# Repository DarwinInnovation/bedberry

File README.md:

# bedberry

PCB for intelligent electric bed/chair control. A board to allow those with disabilities
a number of ways to control electric beds, chairs etc.

Based around the [Raspberry Pi Zero 2W](https://www.raspberrypi.com/products/raspberry-pi-zero-2-w/) it is designed to allow abilities such as:

- Voice service (e.g. Alexa) control of the bed.
- Control of all the bed's function from simple buttons or pressure pads.
- Link to BLE tilt sensors to allow bed position 'presets'.
- Control of other devices via bluetooth, IR or WiFi, including TVs, lights, SwitchBots etc.

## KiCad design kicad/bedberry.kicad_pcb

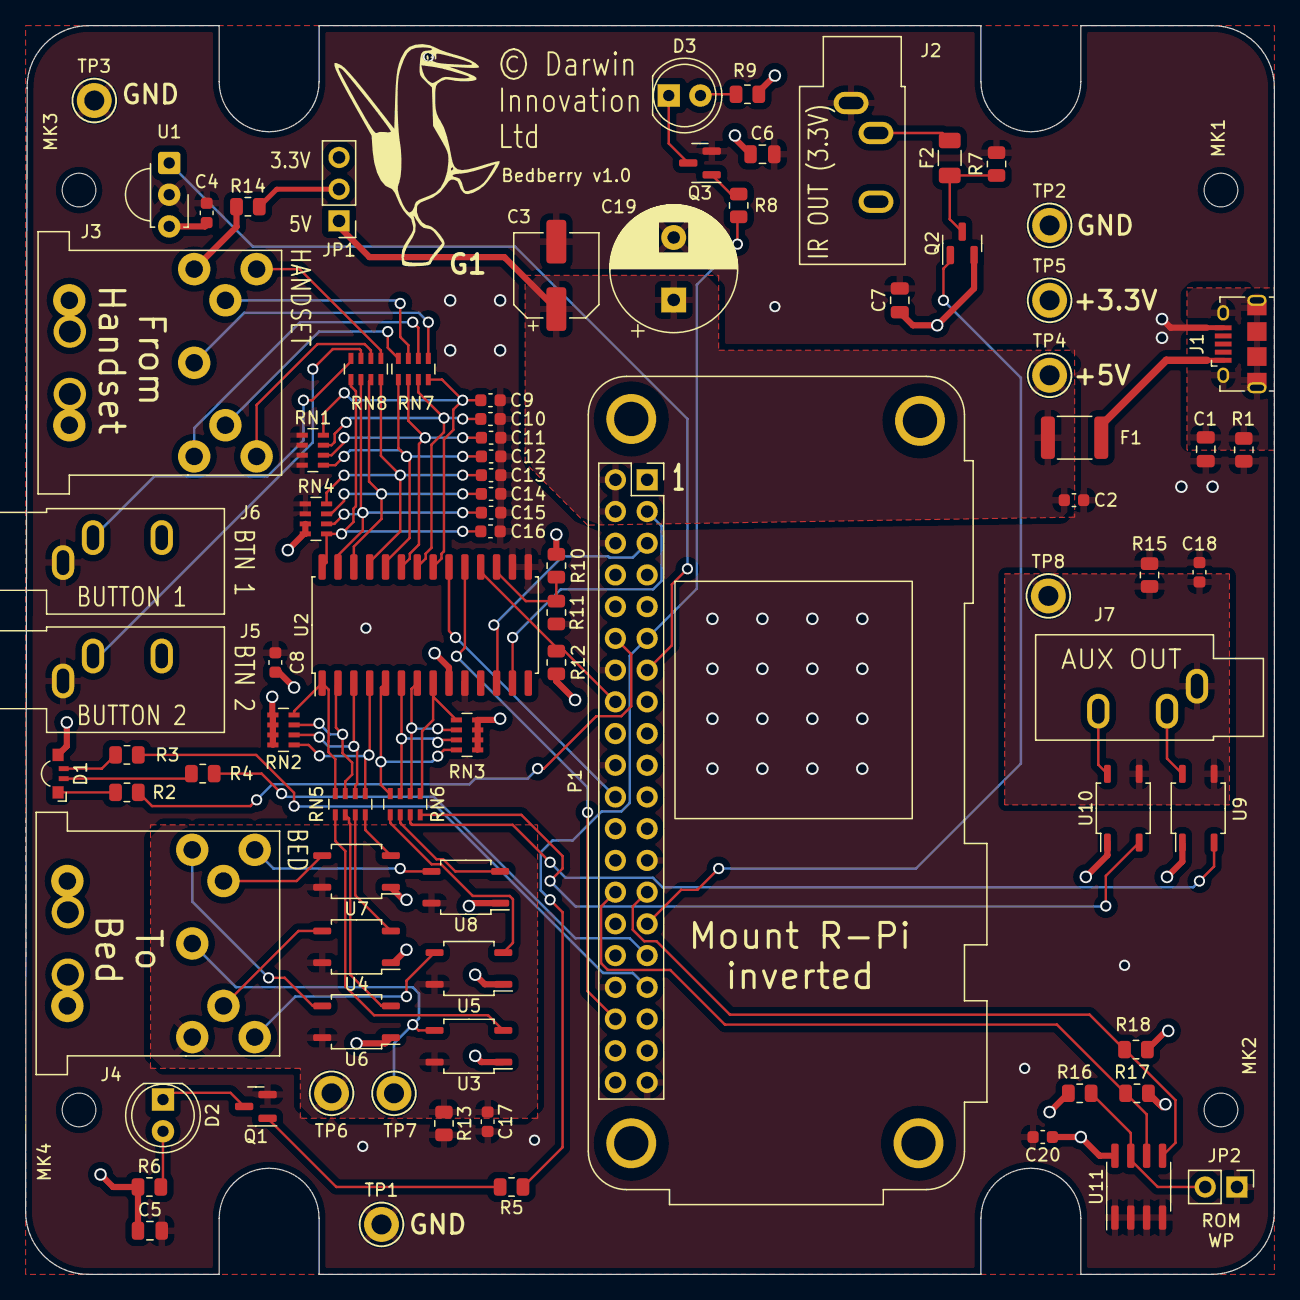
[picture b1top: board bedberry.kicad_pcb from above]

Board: 4 copper layers, 100.0 x 100.0 mm, 88 parts (0 on the bottom side), 75 nets.

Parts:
C1: 1nF 0805; C_0805_2012Metric
C2, C4, C8, C9, C10, C11, C12, C13, C14, C15, C16, C17, C18, C20: 100nF 0603; C_0603_1608Metric
C3: 100uF SMD; CP_Elec_6.3x7.7
C5, C6, C7: 1uF 0805; C_0805_2012Metric
C19: 100uF 10mm TH; CP_Radial_D10.0mm_P5.00mm
D1: KPFA-3010RGBC-11; LED_Kingbright_APFA3010_3x1.5mm_Horizontal
D2, D3: SFH4546; LED_D5.0mm_IRGrey
F1: MP005240; Fuse_1812_4532Metric
F2: 1206L150THWR; Fuse_1206_3216Metric
G1: LOGO; darwin_innovation_logo
J1: USB Micro-B; USB_Micro-B_Amphenol_10118194_Horizontal
J2, J5, J6, J7: SJ1-3533NG; Jack_3.5mm_CUI_SJ1-3533NG_Horizontal
J3, J4: DIN-7; pro-signal_DIN7_Socket
JP1: Jumper; PinHeader_1x03_P2.54mm_Vertical
JP2: Jumper_2_Open; PinHeader_1x02_P2.54mm_Vertical
MK1, MK2, MK3, MK4: M2.5; MountingHole_2.7mm_M2.5
P1: RPi Zero 2 W; Raspberry_Pi_Zero_2W_Socketed_THT_FaceDown_MountingHoles
Q1, Q3: BC817; SOT-23
Q2: MOSFET P-Ch; SOT-23
R1, R13, R15: 1M; R_0805_2012Metric
R2: 120; R_0805_2012Metric
R3, R4, R6, R9, R14: 5.6; R_0805_2012Metric
R5, R8, R16, R17, R18: 1k; R_0805_2012Metric
R7, R10, R11, R12: 10k; R_0805_2012Metric
RN1, RN2, RN3, RN4: 10k; R_Array_Concave_4x0603
RN5, RN6, RN7, RN8: 1.5k; R_Array_Concave_4x0603
TP1, TP2, TP3, TP4, TP5, TP6, TP7, TP8: TestPoint; TestPoint_Keystone_5005-5009_Compact
U1: TSOP382xx; Vishay_MINICAST-3Pin
U2: MCP23017-E/SO; SOIC-28W_7.5x17.9mm_P1.27mm
U3, U4, U5, U6, U7, U8, U9, U10: CPC1017N; SOP-4_3.8x4.1mm_P2.54mm
U11: CAT24C128; SOIC-8_3.9x4.9mm_P1.27mm

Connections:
+3V3: C4.1, C5.1, C6.1, C7.1, C8.1, C20.1, D1.2 (A), JP1.3 (B), P1.1, P1.17, Q2.2 (D), R6.1, R9.1, R10.1, R12.1, R16.1, R17.1, R18.1, RN2.5 (R4.2), RN2.6 (R3.2), RN2.7 (R2.2), RN2.8 (R1.2), RN3.5 (R4.2), RN3.6 (R3.2), RN3.7 (R2.2), RN3.8 (R1.2), RN4.3 (R3.1), RN4.4 (R4.1), TP5.1, U1.3 (Vs), U2.9 (VDD), U3.1, U4.1, U5.1, U6.1, U7.1, U8.1, U9.1, U10.1, U11.8 (VCC)
+5V: C2.1, C3.1, C19.1, F1.2, JP1.1 (A), P1.2, P1.4, TP4.1
/GPIO2_SDA1: P1.3, U2.13 (SDA)
/GPIO3_SCL1: P1.5, U2.12 (SCK)
/GPIO5_AUX_OUT: P1.29, Q2.1 (G)
/GPIO6_LED_B: P1.31, R4.2
/GPIO13_PWM1_LED_G: P1.33, R3.2
/GPIO16_INTB: P1.36, U2.19 (INTB)
/GPIO17_IR_OUT: P1.11, R5.1, R8.1
/GPIO18_PWM0_LED_R: P1.12, R2.2
/GPIO23_RESET: P1.16, R12.2, U2.18 (~RESET)
/GPIO25_INTA: P1.22, U2.20 (INTA)
/GPIO27_IR_IN: P1.13, U1.1 (OUT)
/ID_SC: P1.28, R17.2, U11.6 (SCL)
/ID_SD: P1.27, R18.2, U11.5 (SDA)
/IO_Bed/DIN_IN_COMMON: J3.1, R14.1
/IO_Bed/DIN_OUT_COMMON: C17.1, J4.1, R13.1, TP6.1, U3.4, U4.4, U5.4, U6.4, U7.4, U8.4
/IO_Bed/JACK_OUT_COMMON: C18.1, J7.S, R15.1, TP8.1, U9.3, U10.3
/USB_SHIELD: C1.1, J1.6 (Shield), R1.1
/USB_VBUS: F1.1, J1.1 (VBUS)
GND: C1.2, C2.2, C3.2, C4.2, C5.2, C6.2, C7.2, C8.2, C9.2, C10.2, C11.2, C12.2, C13.2, C14.2, C15.2, C16.2, C17.2, C18.2, C19.2, C20.2, J1.5 (GND), J2.S, J5.S, J6.S, JP2.1 (A), P1.6, P1.9, P1.14, P1.20, P1.25, P1.30, P1.34, P1.39, Q1.2 (E), Q3.2 (E), R1.2, R7.2, R11.2, R13.2, R15.2, RN1.1 (R1.1), RN1.2 (R2.1), RN1.3 (R3.1), RN1.4 (R4.1), RN4.1 (R1.1), RN4.2 (R2.1), TP1.1, TP2.1, TP3.1, U1.2 (GND), U2.10 (VSS), U2.15 (A0), U2.16 (A1), U11.1 (A0), U11.2 (A1), U11.3 (A2), U11.4 (GND)
unnamed: C9.1, RN1.8 (R1.2), RN7.8 (R1.2), U2.21 (GPA0)
unnamed: C10.1, RN1.7 (R2.2), RN7.7 (R2.2), U2.22 (GPA1)
unnamed: C11.1, RN1.6 (R3.2), RN7.6 (R3.2), U2.23 (GPA2)
unnamed: C12.1, RN1.5 (R4.2), RN7.5 (R4.2), U2.24 (GPA3)
unnamed: C13.1, RN4.8 (R1.2), RN8.8 (R1.2), U2.25 (GPA4)
unnamed: C14.1, RN4.7 (R2.2), RN8.7 (R2.2), U2.26 (GPA5)
unnamed: C15.1, RN4.6 (R3.2), RN8.6 (R3.2), U2.27 (GPA6)
unnamed: C16.1, RN4.5 (R4.2), RN8.5 (R4.2), U2.28 (GPA7)
unnamed: D2.1 (K), Q1.3 (C)
unnamed: D2.2 (A), R6.2
unnamed: D3.1 (K), Q3.3 (C)
unnamed: D3.2 (A), R9.2
unnamed: F2.1, Q2.3 (S), R7.1
unnamed: F2.2, J2.T
unnamed: J3.2, RN7.1 (R1.1)
unnamed: J3.3, RN7.2 (R2.1)
unnamed: J3.4, RN7.3 (R3.1)
unnamed: J3.5, RN7.4 (R4.1)
unnamed: J3.6, RN8.1 (R1.1)
unnamed: J3.7, RN8.2 (R2.1)
unnamed: J4.2, TP7.1, U3.3
unnamed: J4.3, U6.3
unnamed: J4.4, U4.3
unnamed: J4.5, U7.3
unnamed: J4.6, U5.3
unnamed: J4.7, U8.3
unnamed: J5.T, RN8.3 (R3.1)
unnamed: J6.T, RN8.4 (R4.1)
unnamed: J7.R, U10.4
unnamed: J7.T, U9.4
unnamed: JP1.2 (C), R14.2
unnamed: JP2.2 (B), R16.2, U11.7 (WP)
unnamed: Q1.1 (B), R5.2
unnamed: Q3.1 (B), R8.2
unnamed: D1.1 (R), R2.1
unnamed: D1.3 (G), R3.1
unnamed: D1.4 (B), R4.1
unnamed: R10.2, R11.1, U2.17 (A2)
unnamed: RN2.1 (R1.1), RN5.1 (R1.1), U2.4 (GPB3)
unnamed: RN2.2 (R2.1), RN5.2 (R2.1), U2.3 (GPB2)
unnamed: RN2.3 (R3.1), RN5.3 (R3.1), U2.2 (GPB1)
unnamed: RN2.4 (R4.1), RN5.4 (R4.1), U2.1 (GPB0)
unnamed: RN3.1 (R1.1), RN6.1 (R1.1), U2.8 (GPB7)
unnamed: RN3.2 (R2.1), RN6.2 (R2.1), U2.7 (GPB6)
unnamed: RN3.3 (R3.1), RN6.3 (R3.1), U2.6 (GPB5)
unnamed: RN3.4 (R4.1), RN6.4 (R4.1), U2.5 (GPB4)
unnamed: RN5.5 (R4.2), U3.2
unnamed: RN5.6 (R3.2), U6.2
unnamed: RN5.7 (R2.2), U4.2
unnamed: RN5.8 (R1.2), U7.2
unnamed: RN6.5 (R4.2), U5.2
unnamed: RN6.6 (R3.2), U8.2
unnamed: RN6.7 (R2.2), U9.2
unnamed: RN6.8 (R1.2), U10.2

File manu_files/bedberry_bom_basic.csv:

"Ref","Qnty","Value","Footprint","Description","MPN"
"C1, ","1","1nF 0805","Capacitor_SMD:C_0805_2012Metric","Unpolarized capacitor, small symbol",""
"C2, C4, C8, C9, C10, C11, C12, C13, C14, C15, C16, C17, C18, C20, ","14","100nF 0603","Capacitor_SMD:C_0603_1608Metric","Unpolarized capacitor, small symbol",""
"D1, ","1","KPFA-3010RGBC-11","LED_SMD:LED_Kingbright_APFA3010_3x1.5mm_Horizontal","LED RGB, Common Anode, SMD, 3.0x1.5mm, Horizontal","KPFA-3010RGBC-11"
"F1, ","1","MP005240","Fuse:Fuse_1812_4532Metric","Resettable fuse, polymeric positive temperature coefficient, small symbol","MP005240"
"F2, ","1","1206L150THWR","Fuse:Fuse_1206_3216Metric","Resettable fuse, polymeric positive temperature coefficient, small symbol","1206L150THWR"
"J1, ","1","USB Micro-B","Connector_USB:USB_Micro-B_Amphenol_10118194_Horizontal","USB Micro Type B connector","10118194-0001LF"
"JP1, ","1","Jumper","Connector_PinHeader_2.54mm:PinHeader_1x03_P2.54mm_Vertical","Jumper, 3-pole, pins 1+2 closed/bridged","M20-8770342"
"JP2, ","1","Jumper_2_Open","Connector_PinHeader_2.54mm:PinHeader_1x02_P2.54mm_Vertical","Jumper, 2-pole, open",""
"Q1, Q3, ","2","BC817 SOT23","Package_TO_SOT_SMD:SOT-23","0.8A Ic, 45V Vce, NPN Transistor, SOT-23","BC817-25LT1G"
"Q2, ","1","MOSFET P-Ch SOT23","Package_TO_SOT_SMD:SOT-23","-6.4A Id, -40V Vds, P-Channel MOSFET, SOT-223","DMG2307L-7"
"R1, R13, R15, ","3","1M 0805","Resistor_SMD:R_0805_2012Metric","Resistor",""
"R2, ","1","120 0805","Resistor_SMD:R_0805_2012Metric","Resistor",""
"R3, R4, R6, R9, R14, ","5","5.6 0805","Resistor_SMD:R_0805_2012Metric","Resistor",""
"R5, R8, R16, R17, R18, ","5","1k 0805","Resistor_SMD:R_0805_2012Metric","Resistor",""
"R7, R10, R11, R12, ","4","10k 0805","Resistor_SMD:R_0805_2012Metric","Resistor",""
"RN1, RN2, RN3, RN4, ","4","10k 4x0603","Resistor_SMD:R_Array_Concave_4x0603","4 resistor network, parallel topology","EXBV8V103JV"
"RN5, RN6, RN7, RN8, ","4","1.5k 4x0603","Resistor_SMD:R_Array_Concave_4x0603","4 resistor network, parallel topology","EXB-38V152JV"
"U2, ","1","MCP23017-E/SO","Package_SO:SOIC-28W_7.5x17.9mm_P1.27mm","16-bit I/O expander, I2C, interrupts, w pull-ups, SSOP-28","MCP23017-E/SO"
"U3, U4, U5, U6, U7, U8, U9, U10, ","8","CPC1017N","Package_SO:SOP-4_3.8x4.1mm_P2.54mm","Form A, Solid State Relay (Photo MOSFET) 60V, 0.1A, 16Ohm, SO-4","CPC1017NTR"
"U11, ","1","CAT24C128","Package_SO:SOIC-8_3.9x4.9mm_P1.27mm","128 kb CMOS Serial EEPROM, SOIC-8/TSSOP-8/DFN-8","CAT24C128WI-GT3"

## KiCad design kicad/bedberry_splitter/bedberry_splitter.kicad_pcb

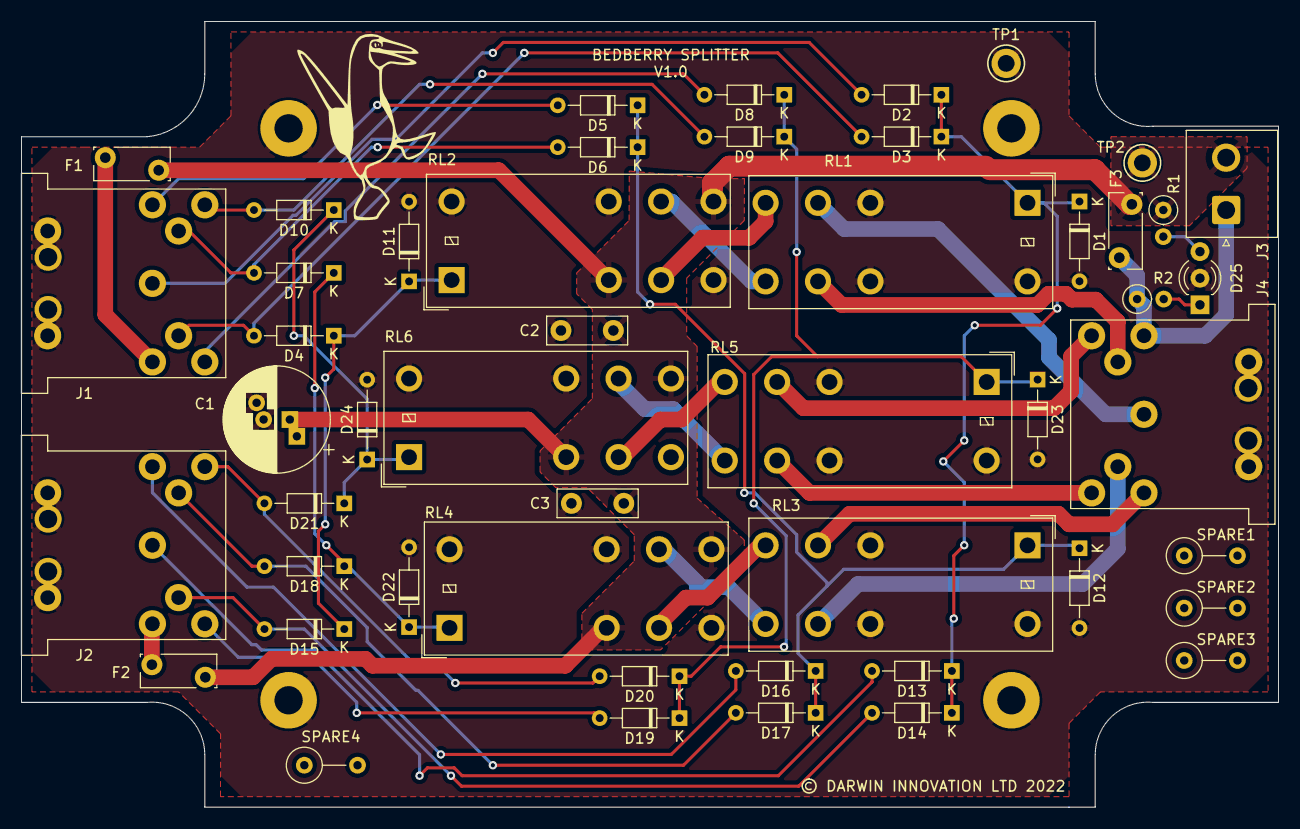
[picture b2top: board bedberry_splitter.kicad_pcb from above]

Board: 2 copper layers, 120.0 x 75.0 mm, 53 parts (0 on the bottom side), 37 nets.

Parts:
C1: 470uF; CP_Radial_D10.0mm_P2.50mm_P5.00mm
C2, C3: 47nF; C_Disc_D7.5mm_W2.5mm_P5.00mm
D1, D2, D3, D4, D5, D6, D7, D8, D9, D10, D11, D12, D13, D14, D15, D16, D17, D18, D19, D20, D21, D22, D23, D24: 1N4002; D_DO-34_SOD68_P7.62mm_Horizontal
D25: LED_Dual_AKA; LED_D3.0mm-3
F1, F2, F3: Polyfuse; Fuse_Bourns_MF-RG300
H3: locked; MountingHole_2.7mm_M2.5_Pad
J1, J2, J4: DIN-7_with_Shield; pro-signal_DIN7_Socket
J3: Screw_Terminal_01x02; JST_NV_B02P-NV_1x02_P5.00mm_Vertical
R1, R2: 5k6; R_Axial_DIN0207_L6.3mm_D2.5mm_P2.54mm_Vertical
RL1, RL2, RL3, RL4, RL5, RL6: G2RL-2-ASI-DC24; Relay_DPDT_Omron_G2RL
SPARE1, SPARE2, SPARE3, SPARE4: R_Axial_DIN0309_L9.0mm_D3.2mm_P5.08mm_Vertical
TP1, TP2: TestPoint; TestPoint_Keystone_5005-5009_Compact
locked: MountingHole_Pad; MountingHole_2.7mm_M2.5_Pad
locked#2: locked; MountingHole_2.7mm_M2.5_Pad
locked#3: MountingHole_Pad; MountingHole_2.7mm_M2.5_Pad

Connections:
+VDC: C1.1, C2.1, C3.1, F1.1, F2.1, F3.1, J3.2, R1.1, RL2.2, RL2.5, RL4.2, RL4.5, RL6.2, RL6.5, TP2.1
/BED_M1_DN: J4.4, RL1.6
/BED_M1_UP: J4.2, RL1.3
/BED_M2_DN: J4.5, RL3.6
/BED_M2_UP: J4.3, RL3.3
/BED_M3_DN: J4.7, RL5.6
/BED_M3_UP: J4.6, RL5.3
/BED_PWR: F3.2, J3.1, J4.1, R2.1
/COIL_M1_A: D4.1 (K), D11.1 (K), D15.1 (K), RL2.1
/COIL_M1_B: D1.1 (K), D2.1 (K), D3.1 (K), D13.1 (K), D14.1 (K), RL1.1
/COIL_M2_A: D7.1 (K), D18.1 (K), D22.1 (K), RL4.1
/COIL_M2_B: D5.1 (K), D6.1 (K), D12.1 (K), D16.1 (K), D17.1 (K), RL3.1
/COIL_M3_A: D10.1 (K), D21.1 (K), D24.1 (K), RL6.1
/COIL_M3_B: D8.1 (K), D9.1 (K), D19.1 (K), D20.1 (K), D23.1 (K), RL5.1
/HS1_M1_DN: D3.2 (A), D4.2 (A), J1.4
/HS1_M1_UP: D2.2 (A), J1.2
/HS1_M2_DN: D6.2 (A), D7.2 (A), J1.5
/HS1_M2_UP: D5.2 (A), J1.3
/HS1_M3_DN: D9.2 (A), D10.2 (A), J1.7
/HS1_M3_UP: D8.2 (A), J1.6
/HS1_PWR: F1.2, J1.1
/HS2_M1_DN: D14.2 (A), D15.2 (A), J2.4
/HS2_M1_UP: D13.2 (A), J2.2
/HS2_M2_DN: D17.2 (A), D18.2 (A), J2.5
/HS2_M2_UP: D16.2 (A), J2.3
/HS2_M3_DN: D20.2 (A), D21.2 (A), J2.7
/HS2_M3_UP: D19.2 (A), J2.6
/HS2_PWR: F2.2, J2.1
GND: C1.2, C2.2, C3.2, D1.2 (A), D11.2 (A), D12.2 (A), D22.2 (A), D23.2 (A), D24.2 (A), D25.2 (K), H3.1, J1.8, J2.8, J4.8, RL1.2, RL1.7, RL1.8, RL2.4, RL2.7, RL2.8, RL3.2, RL3.7, RL3.8, RL4.4, RL4.7, RL4.8, RL5.2, RL5.7, RL5.8, RL6.4, RL6.7, RL6.8, TP1.1, locked.1, locked#2.1, locked#3.1
unnamed: D25.1 (A1), R2.2
unnamed: D25.3 (A2), R1.2
unnamed: RL1.4, RL2.3
unnamed: RL1.5, RL2.6
unnamed: RL3.4, RL4.3
unnamed: RL3.5, RL4.6
unnamed: RL5.4, RL6.3
unnamed: RL5.5, RL6.6

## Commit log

2022-02-24 Add KiCad files
2022-02-24 update gitignore
2022-02-24 Small updates/descriptions
2022-02-28 updated design
2022-02-28 add manufacturing files
2022-02-28 add 3D render
2022-03-01 crop image
2022-03-28 BOM changes; RPi thermal gap
2022-03-28 Add basic BoM
2022-07-14 add node_modules
2022-07-14 add software
2022-07-20 update tests
2022-07-20 update packages
2022-07-20 try without INTCAP
2022-07-20 Multibutton changes
2022-07-20 Add tests to launch
2022-08-16 pre-relay change
2022-08-22 start changing relays
2022-08-25 Add BedBerry Splitter v1.0
2022-09-21 rename to okin
2022-09-21 stop when true
2022-09-21 add URL action
2022-09-21 init write bits
2022-09-21 just tsc on compile
2022-09-28 add systemd file
2022-09-28 correct directions
2022-09-28 turn down logging
2022-09-28 fix url actions
2022-09-28 logging changes

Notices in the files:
kicad/bedberry.kicad_pcb:
© Darwin
kicad/bedberry_splitter/bedberry_splitter.kicad_pcb:
© DARWIN INNOVATION LTD 2022
